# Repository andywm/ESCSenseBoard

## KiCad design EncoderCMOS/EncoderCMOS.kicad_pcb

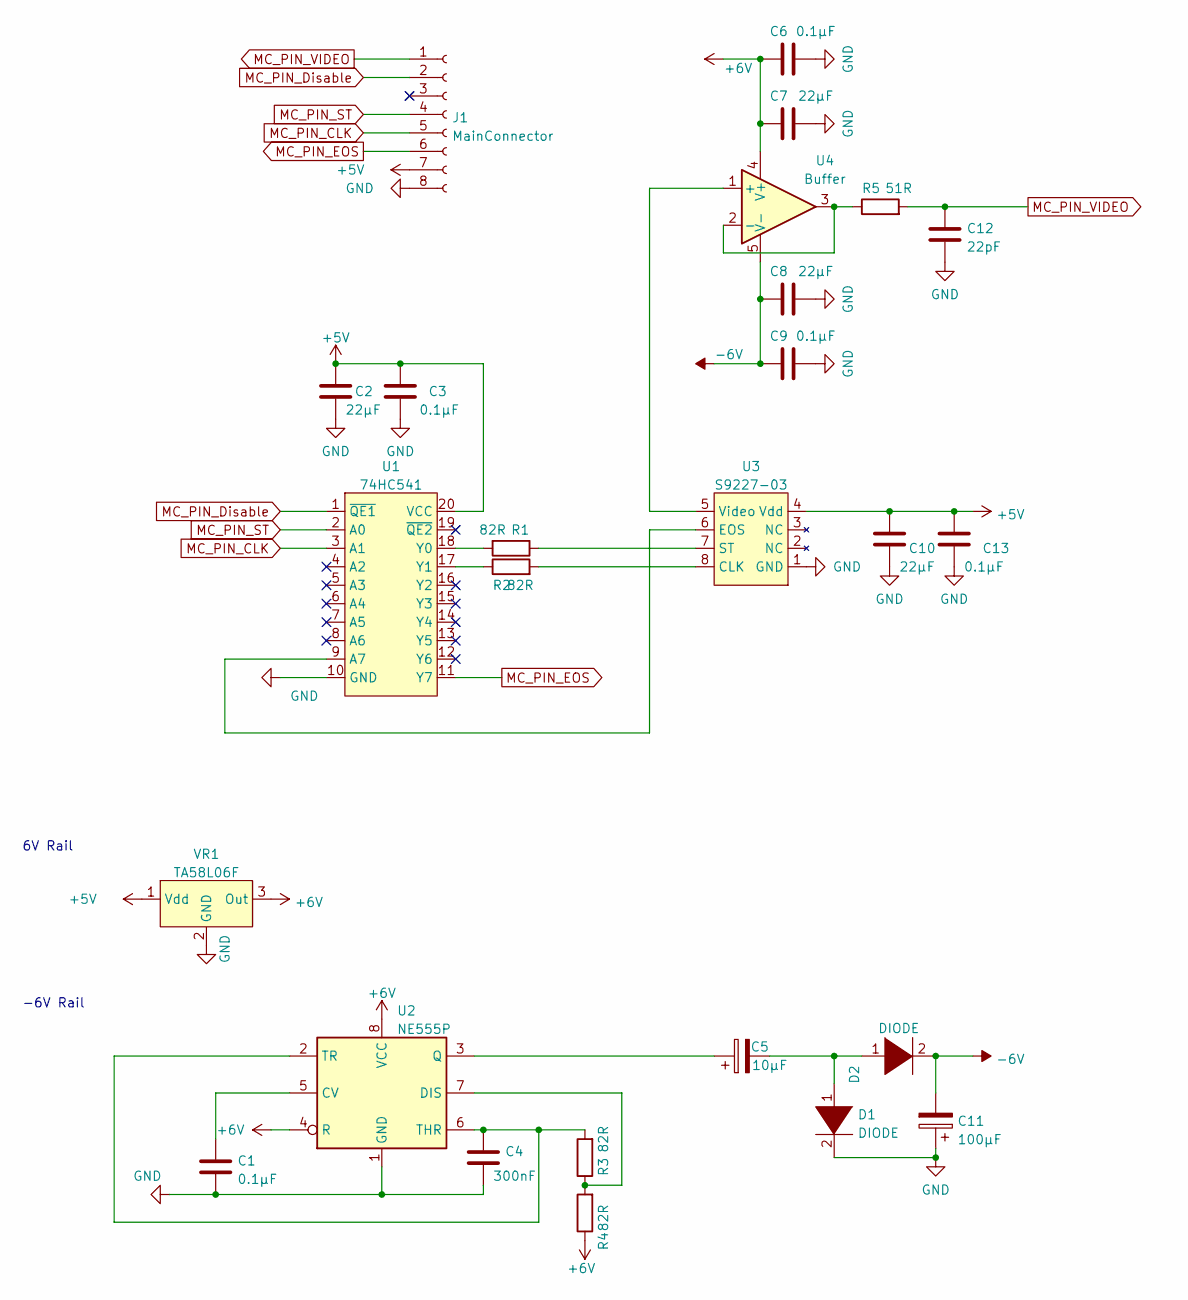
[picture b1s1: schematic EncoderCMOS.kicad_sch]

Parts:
C1, C3, C6, C9, C13: 0.1μF; C_1206_3216Metric_Pad1.33x1.80mm_HandSolder
C2, C7, C8, C10: 22μF; C_1206_3216Metric_Pad1.33x1.80mm_HandSolder
C4: 300nF; C_1206_3216Metric_Pad1.33x1.80mm_HandSolder
C5: 10μF; C_1206_3216Metric_Pad1.33x1.80mm_HandSolder
C11: 100μF; C_1206_3216Metric_Pad1.33x1.80mm_HandSolder
C12: 22pF; C_1206_3216Metric_Pad1.33x1.80mm_HandSolder
D1, D2: DIODE; D_1206_3216Metric_Pad1.42x1.75mm_HandSolder
J1: MainConnector; JST_PH_S8B-PH-K_1x08_P2.00mm_Horizontal
R1, R2, R3, R4: 82R; R_1206_3216Metric_Pad1.30x1.75mm_HandSolder
R5: 51R; R_1206_3216Metric_Pad1.30x1.75mm_HandSolder
U1: 74HC541; SSOP-20_4.4x6.5mm_P0.65mm
U2: NE555P; DIP-8_W7.62mm
U3: S9227-03; DIP-8_W7.62mm
U4: Buffer; SOIC-8_3.9x4.9mm_P1.27mm
VR1: TA58L06F; ATPAK-2

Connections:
+5V: C2.1, C3.1, C10.1, C13.1, J1.7, U1.20 (VCC), U3.4 (Vdd), VR1.1 (Vdd)
+6V: C6.1, C7.1, R4.1, U2.4 (R), U2.8 (VCC), U4.4 (V+), VR1.3 (Out)
-6V: C8.1, C9.1, C11.2, D2.2 (A), U4.5 (V-)
GND: C1.2, C2.2, C3.2, C4.2, C6.2, C7.2, C8.2, C9.2, C10.2, C11.1, C12.2, C13.2, D1.2 (A), J1.8, U1.10 (GND), U2.1 (GND), U3.1 (GND), VR1.2 (GND)
MC_PIN_CLK: J1.5, U1.3 (A1)
MC_PIN_Disable: J1.2, U1.1 (~QE1)
MC_PIN_EOS: J1.6, U1.11 (Y7)
MC_PIN_ST: J1.4, U1.2 (A0)
MC_PIN_VIDEO: C12.1, J1.1, R5.2
unnamed: C1.1, U2.5 (CV)
unnamed: C4.1, R3.2, U2.2 (TR), U2.6 (THR)
unnamed: C5.1, U2.3 (Q)
unnamed: C5.2, D1.1 (K), D2.1 (K)
unnamed: R1.1, U3.7 (ST)
unnamed: R2.2, U3.8 (CLK)
unnamed: R3.1, R4.2, U2.7 (DIS)
unnamed: R5.1, U4.2 (-), U4.3
unnamed: U1.9 (A7), U3.6 (EOS)
unnamed: R2.1, U1.17 (Y1)
unnamed: R1.2, U1.18 (Y0)
unnamed: U3.5 (Video), U4.1 (+)

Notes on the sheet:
6V Rail
-6V Rail

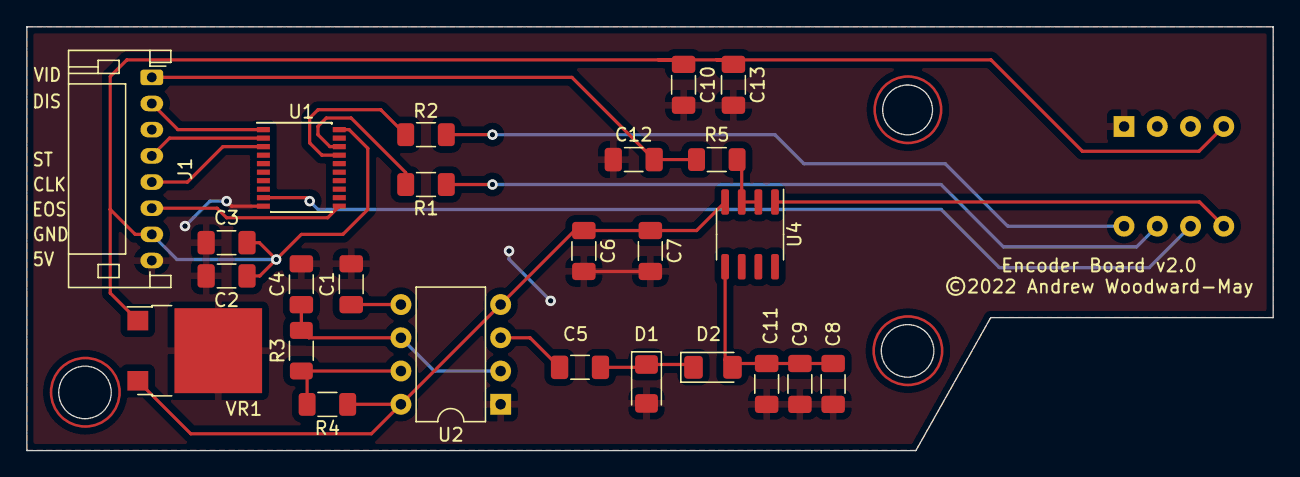
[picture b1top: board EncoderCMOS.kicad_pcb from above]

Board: 2 copper layers, 95.2 x 32.4 mm, 26 parts (1 on the bottom side), 21 nets.

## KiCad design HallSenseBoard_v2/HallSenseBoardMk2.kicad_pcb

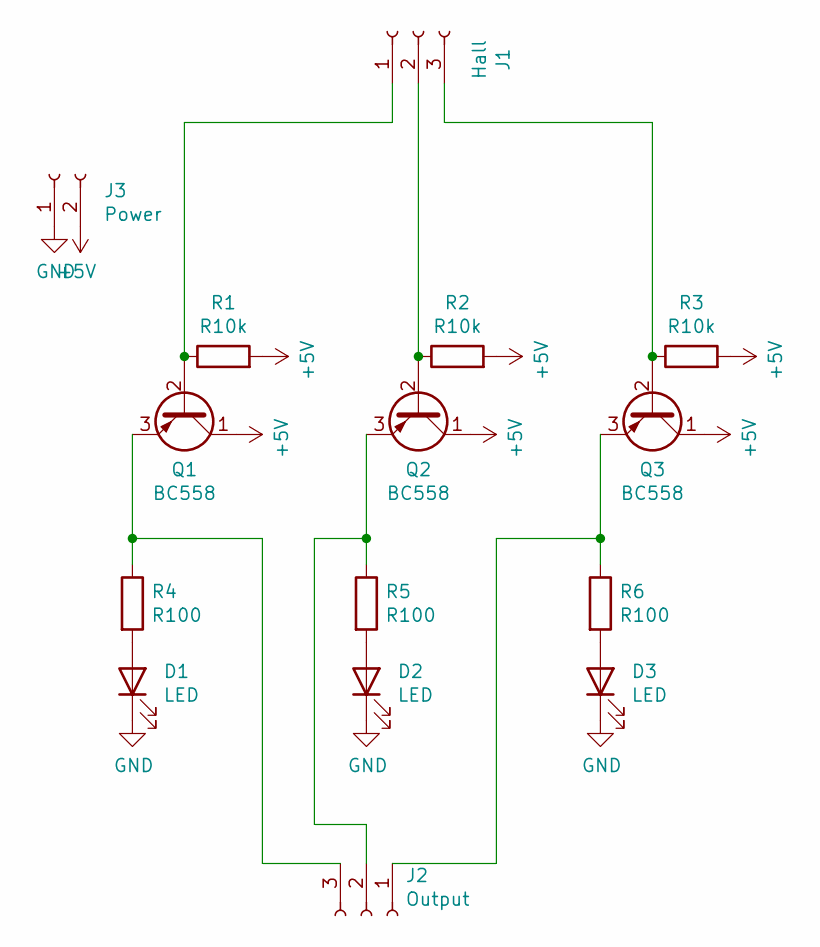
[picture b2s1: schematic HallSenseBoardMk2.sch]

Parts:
D1, D2, D3: LED; LED_D3.0mm
J1: Hall; SolderWire-0.5sqmm_1x03_P4.6mm_D0.9mm_OD2.1mm_Relief
J2: Output; JST_XH_B3B-XH-A_1x03_P2.50mm_Vertical
J3: Power; JST_XH_B2B-XH-A_1x02_P2.50mm_Vertical
Q1, Q2, Q3: BC558; TO-92_Inline
R1, R2, R3: R10k; R_Axial_DIN0309_L9.0mm_D3.2mm_P15.24mm_Horizontal
R4, R5, R6: R100; R_Axial_DIN0207_L6.3mm_D2.5mm_P10.16mm_Horizontal

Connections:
+5V: J3.2, Q1.1 (C), Q2.1 (C), Q3.1 (C), R1.2, R2.2, R3.2
GND: D1.1 (K), D2.1 (K), D3.1 (K), J3.1
unnamed: D1.2 (A), R4.2
unnamed: D2.2 (A), R5.2
unnamed: D3.2 (A), R6.2
unnamed: J1.1, Q1.2 (B), R1.1
unnamed: J1.2, Q2.2 (B), R2.1
unnamed: J1.3, Q3.2 (B), R3.1
unnamed: J2.1, Q3.3 (E), R6.1
unnamed: J2.2, Q2.3 (E), R5.1
unnamed: J2.3, Q1.3 (E), R4.1

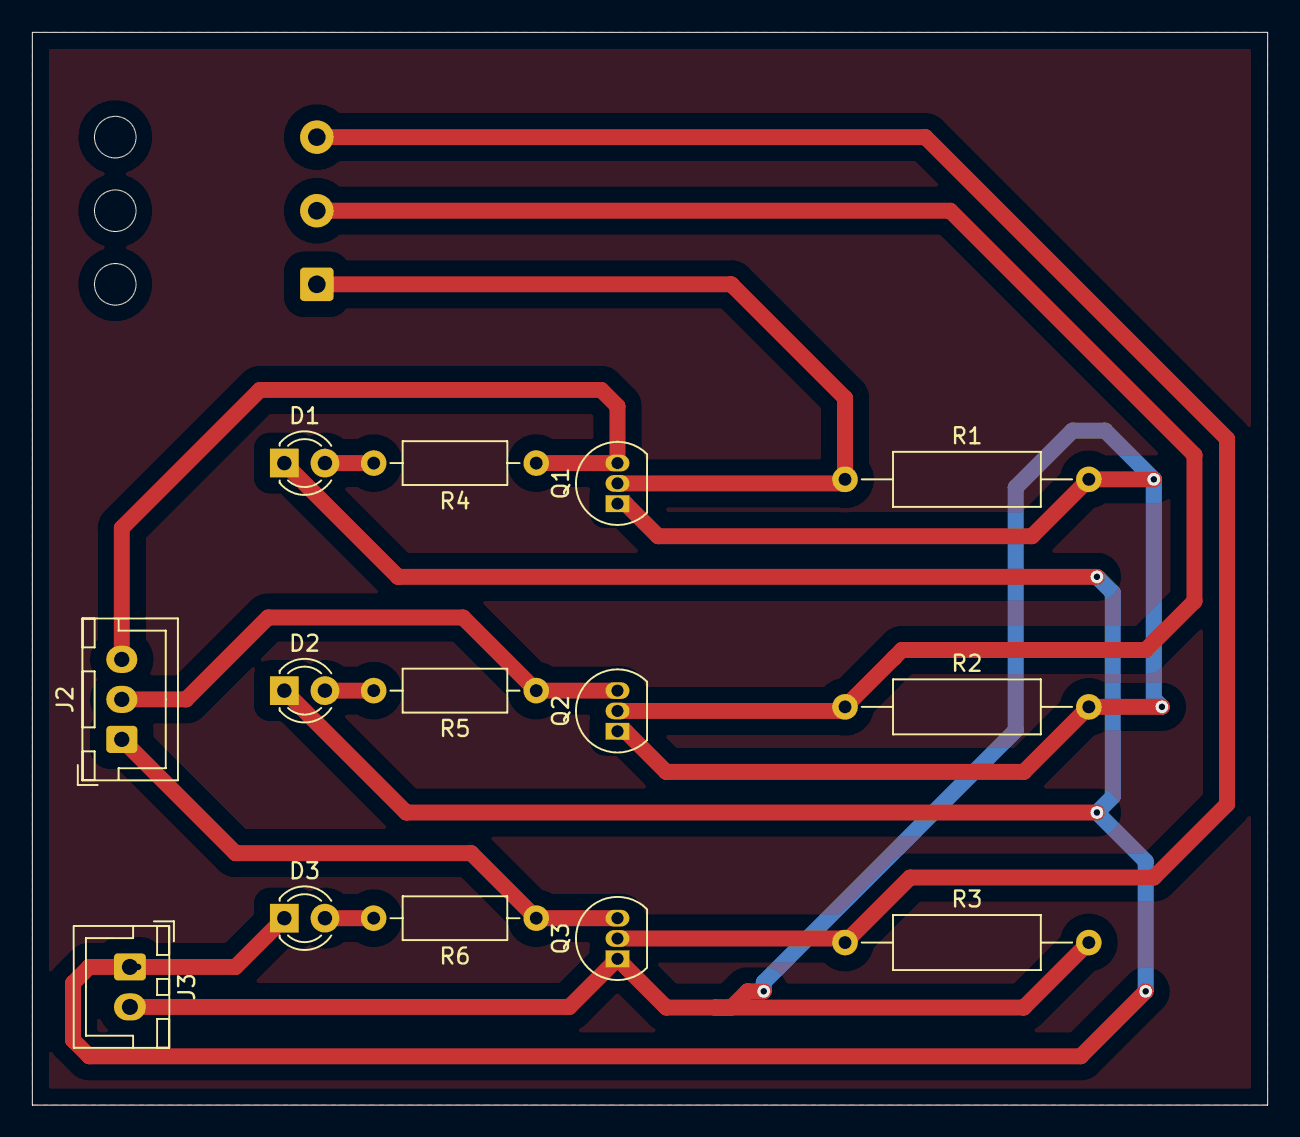
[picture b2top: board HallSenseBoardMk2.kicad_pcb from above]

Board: 2 copper layers, 77.2 x 67.1 mm, 15 parts (1 on the bottom side), 11 nets.

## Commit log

2022-02-26 add older encoder prototypes
2022-03-12 fill out board layout, add plot files

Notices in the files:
EncoderCMOS/EncoderCMOS.kicad_pcb:
©2022 Andrew Woodward-May
